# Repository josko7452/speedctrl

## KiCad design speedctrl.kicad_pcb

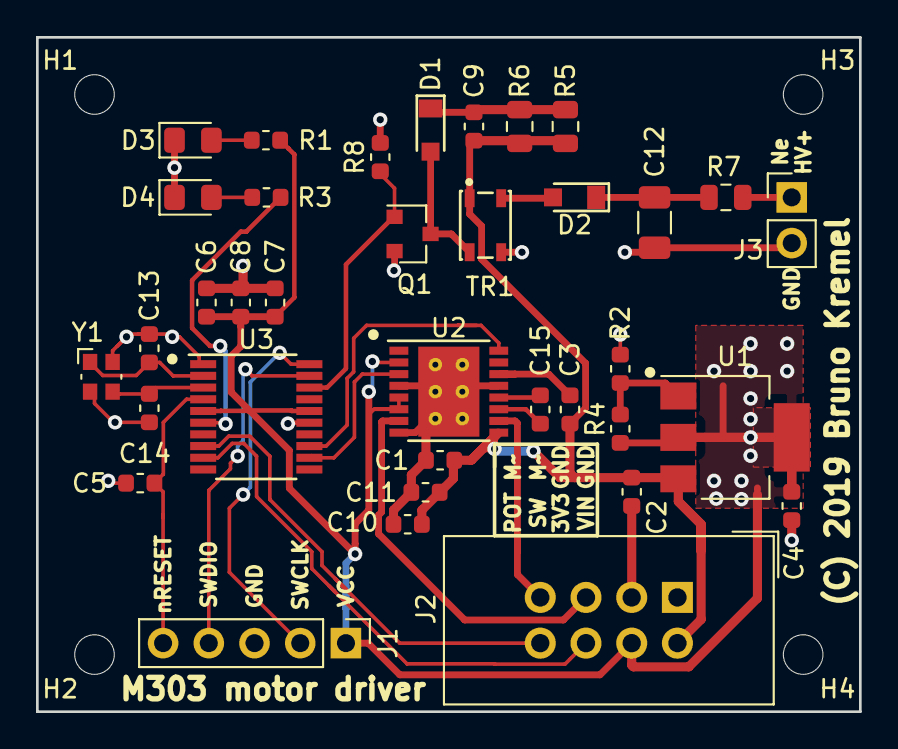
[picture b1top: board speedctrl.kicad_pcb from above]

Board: 2 copper layers, 45.7 x 37.5 mm, 40 parts (0 on the bottom side), 27 nets.

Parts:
C1, C3, C5, C8, C15: 100n; C_0603_1608Metric
C2, C6: 1u; C_0603_1608Metric
C4, C10, C11: 4u7; C_0603_1608Metric
C7: 10n; C_0603_1608Metric
C9: 0.1u/50V; C_0603_1608Metric
C12: 10n/200V; C_1206_3216Metric
C13, C14: 10pF; C_0603_1608Metric
D1, D2: DA2JF8100L; Diode_SMini2-F5-B
D3: HSMY-C170; LED_0805_2012Metric_Pad1.15x1.40mm_HandSolder
D4: HSMG-C170; LED_0805_2012Metric_Pad1.15x1.40mm_HandSolder
H1, H2, H3, H4: MountingHole; MountingHole_2.2mm_M2
J1: Conn_01x05; PinHeader_1x05_P2.54mm_Vertical
J2: Conn_02x04_Odd_Even; IDC-Header_2x04_P2.54mm_Vertical
J3: Conn_01x02; PinHeader_1x02_P2.54mm_Vertical
Q1: BSS138; SOT-23
R1, R3, R4: 330; R_0603_1608Metric
R2: 560; R_0603_1608Metric
R5, R6: 10k; R_0805_2012Metric
R7: 220k; R_0805_2012Metric
R8: 10k; R_0603_1608Metric
TR1: ATB322524-0110; ATB3225
U1: LM317_3PinPackage; SOT-223-3_TabPin2
U2: DRV8816PWPR; HTSSOP-16-1EP_4.4x5mm_P0.65mm_EP3.4x5mm_Mask2.46x2.31mm_The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
U3: STM32F070F6Px; TSSOP-20_4.4x6.5mm_P0.65mm
Y1: Crystal_GND24; Crystal_SMD_Abracon_ABM10-4Pin_2.5x2.0mm

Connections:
+3V3: C4.1, C6.1, C7.1, C8.1, J1.1, J2.4, R1.2, R4.1, U1.2, U2.2, U2.5, U2.6, U3.5, U3.16
+24V: C1.1, C2.1, C3.1, C9.1, C10.1, C11.1, J2.2, R5.1, R6.1, TR1.1, U1.3, U2.9
/33-45SW: J2.6, U3.9
/SPEED_POT_SLIDER: J2.8, U3.8
/SWCLK: J1.2, U3.20
/SWDIO: J1.4, U3.19
GND: C1.2, C2.2, C4.2, C5.2, C6.2, C7.2, C8.2, C10.2, C11.2, C12.2, C13.2, C14.2, D3.1, D4.1, J1.3, J2.1, J2.3, J3.2, Q1.2, R2.2, R8.2, TR1.3, U2.4, U2.8, U2.13, U2.17, U3.1, U3.15, Y1.2, Y1.4
unnamed: C3.2, U2.14
unnamed: C5.1, J1.5, U3.4
unnamed: C9.2, D1.1, R5.2, R6.2
unnamed: C12.1, D2.1, R7.2
unnamed: C13.1, U3.2, Y1.1
unnamed: C14.1, U3.3, Y1.3
unnamed: C15.1, U2.11
unnamed: C15.2, U2.12
unnamed: D1.2, Q1.3, TR1.4
unnamed: D2.2, TR1.2
unnamed: D3.2, R1.1
unnamed: D4.2, R3.2
unnamed: J2.5, U2.7
unnamed: J2.7, U2.10
unnamed: J3.1, R7.1
unnamed: Q1.1, R8.1, U3.18
unnamed: R2.1, R4.2, U1.1
unnamed: R3.1, U3.6
unnamed: U2.3, U3.12
unnamed: U2.16, U3.13

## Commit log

2018-11-25 Add gitignore
2018-11-25 Add kicad libraries as submodules
2018-11-25 Add gitattributes
2018-11-25 Add fliters as project-wide
2018-11-25 Add project file, schematics and pcb
2018-11-25 Add *.bck to gitignore
2018-11-25 Add more gitignores
2018-11-25 Add custom library
2018-11-25 Add sym-lib-table
2018-11-25 Fix the submodule mess
2018-11-25 Enable autocrlf
2018-11-25 Enable autocrlf in .gitattributes
2018-11-25 Fix missing references
2018-11-25 Add misc_power in kicad-misc-symbols
2018-11-25 Wire-up MCU
2019-01-27 Finalise component values, add decoupling caps
2019-01-27 Update cache
2019-01-27 Fix ERC issues
2019-01-27 Follow upstream libraries
2019-01-27 Assign capacitors and resistors
2019-01-27 Add ATB3225, assign all footprints
2019-01-27 Replace pin sockets with header footprints
2019-01-27 Initial part placement
2019-02-20 Add crystal and mounting holes
2019-02-20 Route PCB
2019-05-12 Use DRV8816 instead of the original driver, use BSS138 for flyback
2019-05-12 Update misc library

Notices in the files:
speedctrl.kicad_pcb:
(C) 2019 Bruno Kremel
